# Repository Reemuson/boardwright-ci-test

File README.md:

<h1 align="center">FIC-100A</h1>

<p align="center">
  
&nbsp; &nbsp; &nbsp; &nbsp;
  
</p>

***

## SPECIFICATIONS

| Parameter | Value | 
| --- | --- |
| Revision | 0.1.3 |
| Board revision | A |
| Release version | 0.1.3 |
| Variant | RELEASED |
| Dimensions | 40.0 x 25.0 mm |

***

## OUTPUTS

Generated manufacturing, schematic, test, and release packages are published
as CI artifacts and GitHub Release assets. The repository source tree remains
the KiCad project and Boardwright workflow configuration.

***

## LEGAL

This repository contains open hardware design files, protected project branding,
and third-party workflow content.

- The primary hardware licence is listed in `LICENSE`.
- Project-specific scope notes, branding exclusions, compatibility wording,
  non-affiliation wording, and safety notes are in `NOTICE.md`.
- Third-party copyright and licence notices are preserved in
  `THIRD_PARTY_NOTICES.md`.

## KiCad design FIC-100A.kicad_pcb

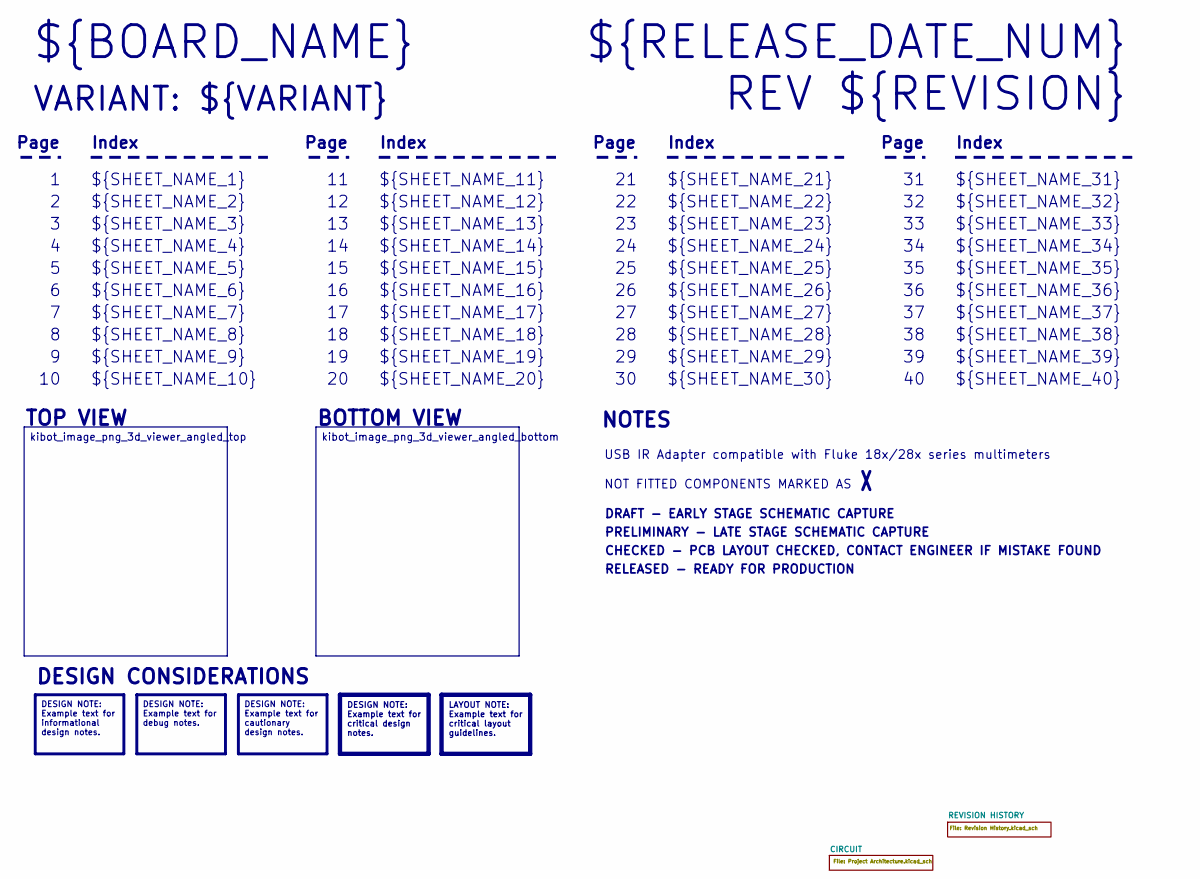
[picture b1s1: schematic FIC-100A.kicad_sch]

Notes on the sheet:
VARIANT: ${VARIANT}
RELEASED - READY FOR PRODUCTION
${SHEET_NAME_24}
Index
Page
PRELIMINARY - LATE STAGE SCHEMATIC CAPTURE
${SHEET_NAME_22}
DRAFT - EARLY STAGE SCHEMATIC CAPTURE
${SHEET_NAME_12}
${SHEET_NAME_8}
${SHEET_NAME_2}
${SHEET_NAME_5}
${SHEET_NAME_20}
${SHEET_NAME_23}
${RELEASE_DATE_NUM}
${SHEET_NAME_35}
NOT FITTED COMPONENTS MARKED AS
${SHEET_NAME_11}
${SHEET_NAME_6}
${SHEET_NAME_37}
${SHEET_NAME_26}
${SHEET_NAME_36}
REV ${REVISION}
${SHEET_NAME_15}
CHECKED - PCB LAYOUT CHECKED, CONTACT ENGINEER IF MISTAKE FOUND
BOTTOM VIEW
${SHEET_NAME_14}
${SHEET_NAME_21}
${SHEET_NAME_17}
${SHEET_NAME_18}
${SHEET_NAME_7}
${SHEET_NAME_31}
${BOARD_NAME}
NOTES
${SHEET_NAME_40}
${SHEET_NAME_39}
${SHEET_NAME_32}
${SHEET_NAME_1}
${SHEET_NAME_9}
${SHEET_NAME_38}

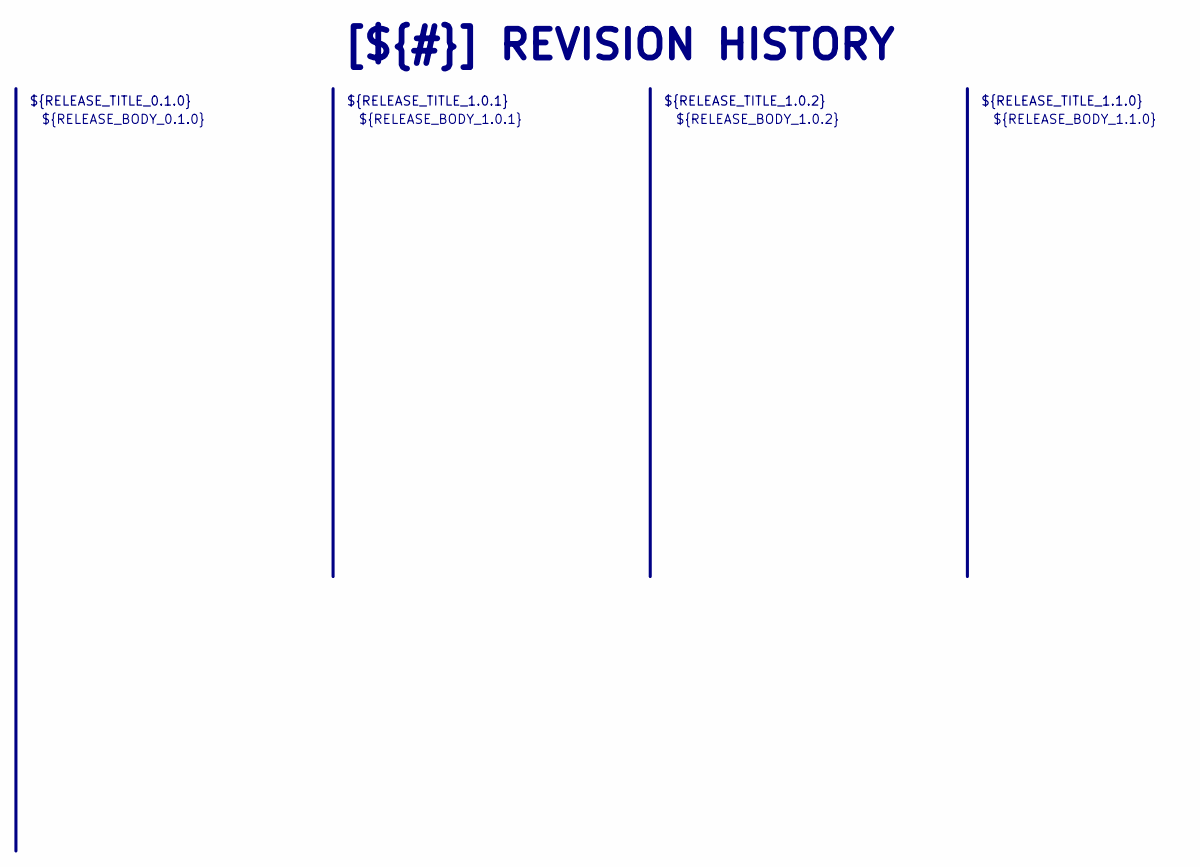
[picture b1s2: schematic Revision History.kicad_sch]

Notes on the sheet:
${RELEASE_BODY_1.1.0}
[${#}] ${TITLE}
${RELEASE_BODY_0.1.0}
${RELEASE_TITLE_1.0.2}
${RELEASE_BODY_1.0.2}
${RELEASE_BODY_1.0.1}
${RELEASE_TITLE_0.1.0}
${RELEASE_TITLE_1.0.1}
${RELEASE_TITLE_1.1.0}

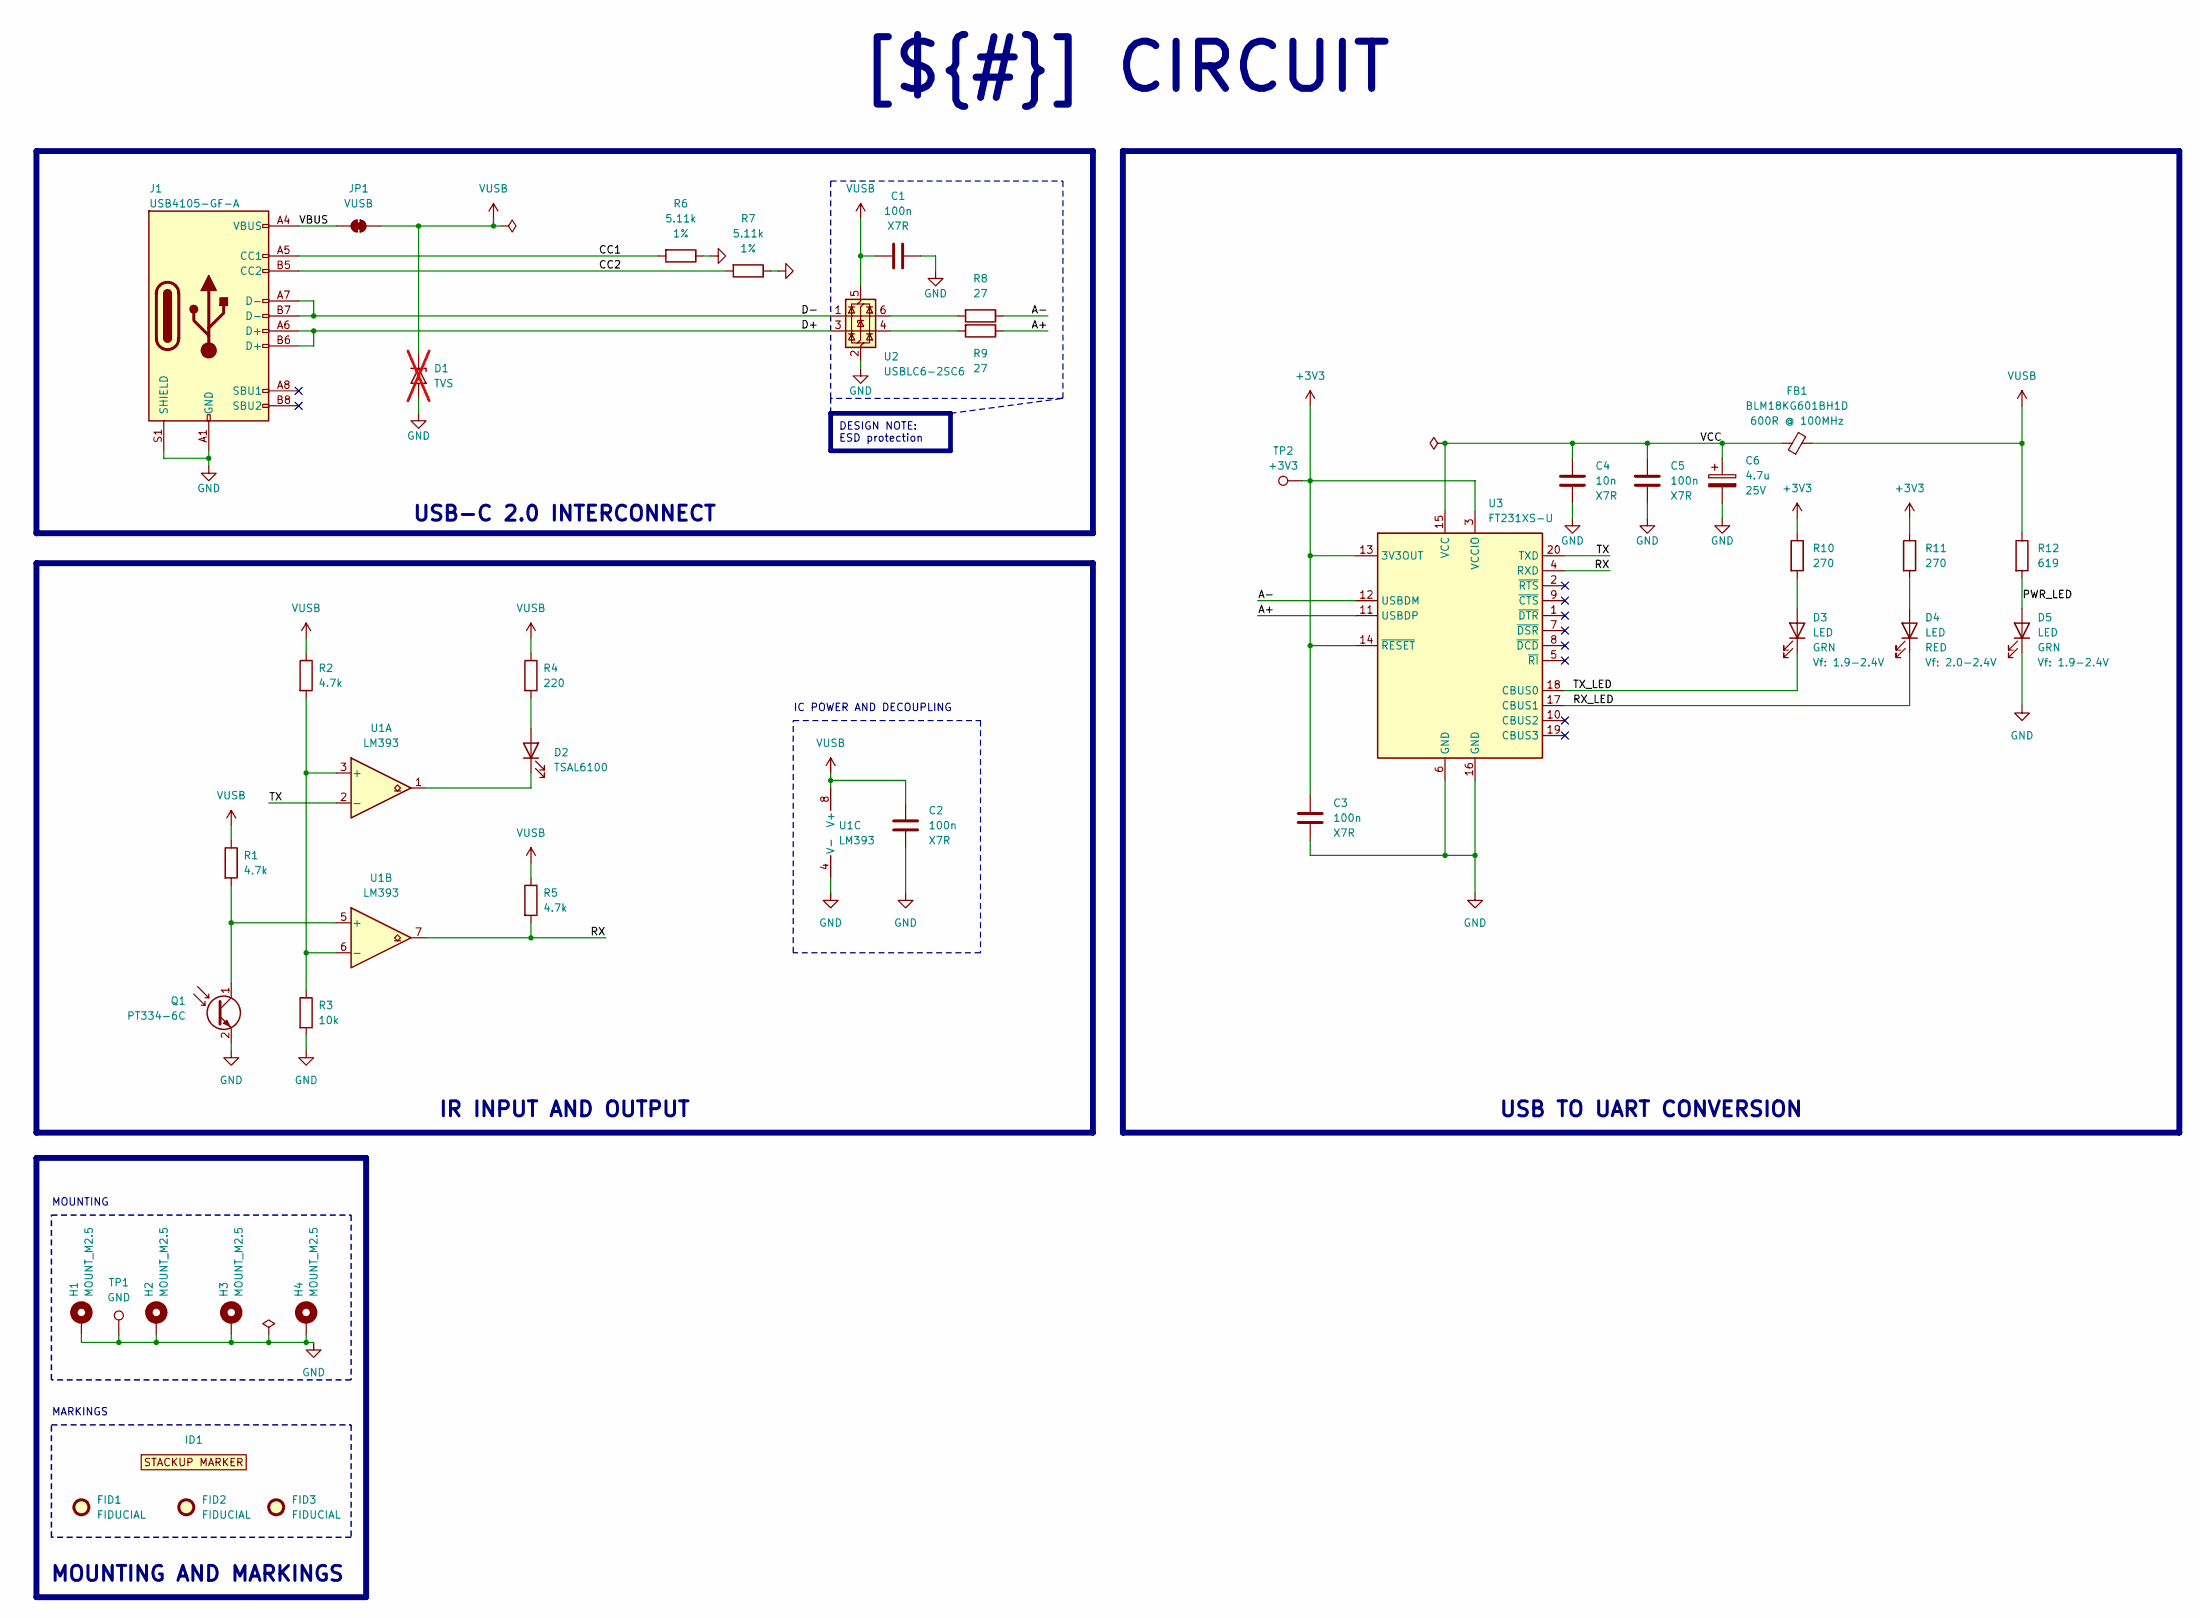
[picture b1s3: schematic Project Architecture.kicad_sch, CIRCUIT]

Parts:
C1, C2, C3, C5: 100n; C_0603_1608Metric; Voltage_Rating 16V; Tolerance 10%; MPN C1608X7R1C104KT
C4: 10n; C_0603_1608Metric; Voltage_Rating 50V; Tolerance 10%; MPN C1608X7R1H103KT
C6: 4.7u; CP_EIA-3216-18_Kemet-A; Tolerance 10%; Voltage 25V; MPN T491A475K025AT
D1: TVS; D_SMB; not fitted
D2: TSAL6100; LED_D5.0mm_IRBlack; MPN TSAL6100
D3, D5: LED; LED_0805_2012Metric; MPN LTST-C170KGKT
D4: LED; LED_0805_2012Metric; MPN LTST-C170KRKT
FB1: BLM18KG601BH1D; L_0603_1608Metric; MPN BLM18KG101JH1D
FID1, FID2, FID3: FIDUCIAL; Fiducial_1mm_Mask2mm
H1, H2, H3, H4: MOUNT_M2.5; MountingHole_2.7mm_M2.5_ISO7380_Pad
ID1: BOARD_STACKUP_MARKER; STACKUP_ID_2L_SML
J1: USB4105-GF-A; USB_C_Receptacle_GCT_USB4105-xx-A_16P_TopMnt_Horizontal; MPN USB4105-GF-A
JP1: VUSB; SolderJumper-2_P1.3mm_Bridged_Pad1.0x1.5mm
Q1: PT334-6C; LED_D5.0mm_Clear; MPN PT334-6C
R1, R2, R5: 4.7k; R_0603_1608Metric; Tolerance 1%
R3: 10k; R_0603_1608Metric; Tolerance 1%
R4: 220; R_0603_1608Metric; Tolerance 1%
R6, R7: 5.11k; R_0603_1608Metric; Tolerance 1%
R8, R9: 27; R_0603_1608Metric; Tolerance 1%
R10, R11: 270; R_0603_1608Metric; Tolerance 1%
R12: 619; R_0603_1608Metric; Tolerance 1%
TP1: GND; TestPoint_Pad_1.0x1.0mm
TP2: +3V3; TestPoint_Pad_D1.0mm
U1: LM393; SOIC-8_3.9x4.9mm_P1.27mm; MPN LM393ADT
U2: USBLC6-2SC6; SOT-23-6; MPN USBLC6-2SC6
U3: FT231XS-U; SSOP-20_3.9x8.7mm_P0.635mm; MPN FT231XS-U

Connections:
+3V3: C3.2, R10.1, R11.1, TP2.1, U3.3 (VCCIO), U3.13 (3V3OUT), U3.14 (~RESET)
/CIRCUIT/A+: R9.1, U3.11 (USBDP)
/CIRCUIT/A-: R8.1, U3.12 (USBDM)
/CIRCUIT/CC1: J1.A5 (CC1), R6.2
/CIRCUIT/CC2: J1.B5 (CC2), R7.2
/CIRCUIT/D+: J1.A6 (D+), J1.B6 (D+), U2.3 (I/O2)
/CIRCUIT/D-: J1.A7 (D-), J1.B7 (D-), U2.1 (I/O1)
/CIRCUIT/PWR_LED: D5.2 (A), R12.2
/CIRCUIT/RX: R5.2, U1.7, U3.4 (RXD)
/CIRCUIT/RX_LED: D4.1 (K), U3.17 (CBUS1)
/CIRCUIT/TX: U1.2 (-), U3.20 (TXD)
/CIRCUIT/TX_LED: D3.1 (K), U3.18 (CBUS0)
/CIRCUIT/VBUS: J1.A4 (VBUS), J1.A9 (VBUS), J1.B4 (VBUS), J1.B9 (VBUS), JP1.1 (A)
/CIRCUIT/VCC: C4.2, C5.2, C6.1, FB1.1, U3.15 (VCC)
GND: C1.1, C2.2, C3.1, C4.1, C5.1, C6.2, D1.2 (A2), D5.1 (K), H1.1, H2.1, H3.1, H4.1, J1.A1 (GND), J1.A12 (GND), J1.B1 (GND), J1.B12 (GND), J1.S1 (SHIELD), Q1.2 (E), R3.2, R6.1, R7.1, TP1.1, U1.4 (V-), U2.2 (GND), U3.6 (GND), U3.16 (GND)
unnamed: D2.2 (A), R4.2
unnamed: D2.1 (K), U1.1
unnamed: D3.2 (A), R10.2
unnamed: D4.2 (A), R11.2
unnamed: Q1.1 (C), R1.2, U1.5 (+)
unnamed: R8.2, U2.6 (I/O1)
unnamed: R9.2, U2.4 (I/O2)
unnamed: R2.2, R3.1, U1.3 (+), U1.6 (-)
VUSB: C1.2, C2.1, D1.1 (A1), FB1.2, JP1.2 (B), R1.1, R2.1, R4.1, R5.1, R12.1, U1.8 (V+), U2.5 (VBUS)

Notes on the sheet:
MOUNTING
IC POWER AND DECOUPLING
MARKINGS
DESIGN NOTE: ESD protection
IR INPUT AND OUTPUT
USB TO UART CONVERSION
USB-C 2.0 INTERCONNECT
MOUNTING AND MARKINGS
[${#}] ${TITLE}

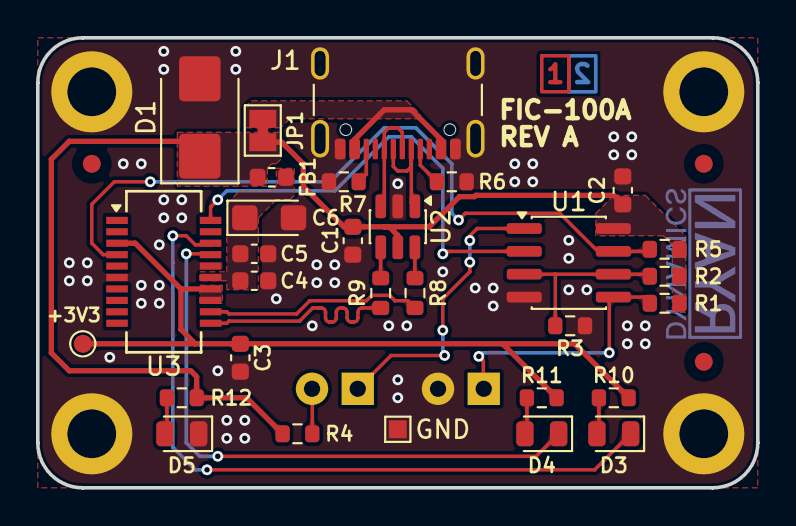
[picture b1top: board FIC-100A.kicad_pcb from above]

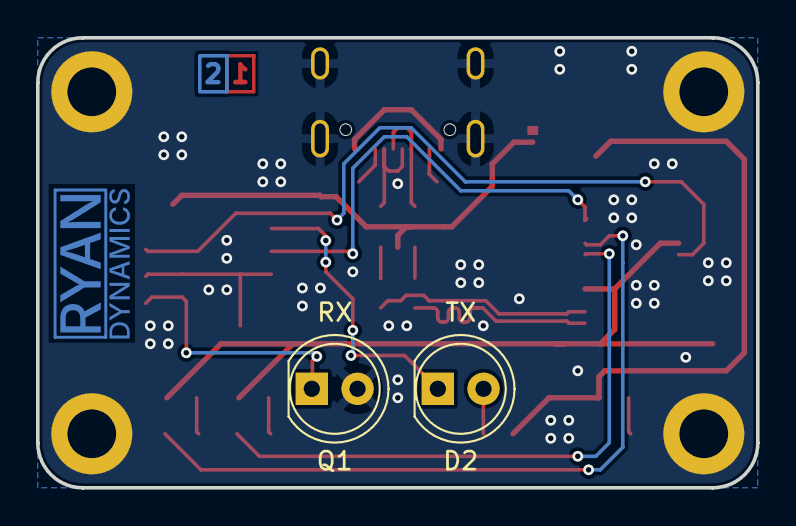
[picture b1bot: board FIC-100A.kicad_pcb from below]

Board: 2 copper layers, 40.0 x 25.0 mm, 40 parts (2 on the bottom side), 24 nets.

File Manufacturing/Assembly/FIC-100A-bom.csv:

Row,Quantity Per PCB,References,Value,Datasheet,Footprint,Description,Manufacturer,MPN,Supplier,SPN,Notes
1,1,C4,10n,https://mm.digikey.com/Volume0/opasdata/d220001/medias/docus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,C_0603_1608Metric,CAP CER 10N 50V X7R 0603,TPK,C1608X7R1H103KT,,,
2,4,C1 C2 C3 C5,100n,https://mm.digikey.com/Volume0/opasdata/d220001/medias/docus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,C_0603_1608Metric,CAP CER 100N 16V X7R 0603,TPK,C1608X7R1C104KT,,,
3,1,C6,4.7u,https://yageogroup.com/content/datasheet/asset/file/KEM_T2005_T491,CP_EIA-3216-18_Kemet-A,CAP TANT 4.7UF 10% 25V 1206,KEMET,T491A475K025AT,DigiKey,399-10128-1-ND,
4,2,D3 D5,LED,https://optoelectronics.liteon.com/upload/download/DS22-2000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,LED_0805_2012Metric,LED GRN CLEAR SMD,Lite-On Inc.,LTST-C170KGKT,DigiKey,160-1414-1-ND,Any low power green 0805 LED
5,1,D4,LED,https://optoelectronics.liteon.com/upload/download/DS-22-99-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,LED_0805_2012Metric,LED RED CLEAR SMD,Lite-On Inc.,LTST-C170KRKT,DigiKey,160-1415-1-ND,Any low power red 0805 LED
6,1,D2,TSAL6100,https://www.vishay.com/docs/81009/tsal6100.pdf,LED_D5.0mm_IRBlack,EMITTER IR 940NM 100MA RADIAL,Vishay Semiconductor Opto Division,TSAL6100,DigiKey,751-1203-ND,
7,1,FB1,BLM18KG601BH1D,https://pim.murata.com/asset/pim4/ferriteBeadInductortypefil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,L_0603_1608Metric,FERRITE BEAD 600 OHM 0603 1LN,Murata Electronics,BLM18KG101JH1D,DigiKey,490-14032-1-ND,
8,1,J1,USB4105-GF-A,https://gct.co/files/specs/usb4105-spec.pdf,USB_C_Receptacle_GCT_USB4105-xx-A_16P_TopMnt_Horizontal,CONN RCP USB2.0 TYP C 16P SMD RA,GCT,USB4105-GF-A,DigiKey,2073-USB4105-GF-ACT-ND,
9,1,Q1,PT334-6C,https://mm.digikey.com/Volume0/opasdata/d220001/medias/docus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,LED_D5.0mm_Clear,SENSOR PHOTO 940NM TOP VIEW RAD,Everlight Electronics Co Ltd,PT334-6C,DigiKey,1080-1159-ND,
10,2,R8 R9,27,https://www.analogtechnologies.com/document/New_Resistor_Kits.pdf,R_0603_1608Metric,RES 27 OHM 1% 1/10W 0603,Analog Technologies,,,,
11,1,R4,220,https://www.analogtechnologies.com/document/New_Resistor_Kits.pdf,R_0603_1608Metric,RES 220 OHM 1% 1/10W 0603,Analog Technologies,,,,
12,2,R10 R11,270,https://www.analogtechnologies.com/document/New_Resistor_Kits.pdf,R_0603_1608Metric,RES 270 OHM 1% 1/10W 0603,Analog Technologies,,,,
13,1,R12,619,https://www.analogtechnologies.com/document/New_Resistor_Kits.pdf,R_0603_1608Metric,RES 619 OHM 1% 1/10W 0603,Analog Technologies,,,,
14,3,R1 R2 R5,4.7k,https://www.analogtechnologies.com/document/New_Resistor_Kits.pdf,R_0603_1608Metric,RES 4.7K OHM 1% 1/10W 0603,Analog Technologies,,,,
15,2,R6 R7,5.11k,https://www.analogtechnologies.com/document/New_Resistor_Kits.pdf,R_0603_1608Metric,RES 5.11K OHM 1% 1/10W 0603,Analog Technologies,,,,
16,1,R3,10k,https://www.analogtechnologies.com/document/New_Resistor_Kits.pdf,R_0603_1608Metric,RES 10K OHM 1% 1/10W 0603,Analog Technologies,,,,
17,1,U3,FT231XS-U,https://ftdichip.com/wp-content/uploads/2025/06/DS_FT231X.pdf,SSOP-20_3.9x8.7mm_P0.635mm,"Full Speed USB to Full Handshake UART, SSOP-20","FTDI, Future Technology Devices International Ltd",FT231XS-U,DigiKey,768-1156-5-ND,
18,1,U1,LM393,http://www.ti.com/lit/ds/symlink/lm393.pdf,SOIC-8_3.9x4.9mm_P1.27mm,IC COMPARATOR 2 GEN PUR 8SOIC,Texas Instruments,LM393ADT,DigiKey,497-4267-1-ND,
19,1,U2,USBLC6-2SC6,https://www.st.com/resource/en/datasheet/cd00050750.pdf,SOT-23-6,TVS DIODE 5.25VWM 17VC SOT23-6,STMicroelectronics,USBLC6-2SC6,DigiKey,497-5235-1-ND,

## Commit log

2026-04-24 chore(template): prepare Boardwright CI test
2026-04-24 fix(ci): make draft preview safe for template smoke tests
2026-04-24 feat(hardware): add Boardwright CI fixture circuit
2026-04-24 fix(revision-history): improve generated entry formatting
2026-04-24 fix(schematic): read sheet titles from kicad source
2026-04-24 ci: remove legacy monolithic workflow
2026-04-24 Update Outputs
2026-04-24 release: prepare 0.1.0
2026-04-24 chore(outputs): update preview outputs
2026-04-25 release: prepare 0.1.1
2026-04-25 feat: add Boardwright-managed release orchestration
2026-04-25 release: prepare 0.1.2 (CHECKED)
2026-04-25 fix: dispatch release workflow after CI tag creation
2026-04-25 fix: keep main to README snapshot outputs
2026-04-25 release: prepare 0.1.3 (CHECKED)
2026-05-24 test: initialize boardwright live testbench
2026-05-24 test: exercise boardwright preview path
2026-05-24 fix: github workflow permission
2026-05-24 fix: hopeful pdf table fixes, non blocking tui fetch
2026-05-24 fix: kicad preflight missing files
2026-05-24 fix: kibot recursion fix?
2026-05-24 fix: refresh default project
2026-05-24 fix: more pdf fixes
2026-05-25 fix: tui test
2026-05-25 test
2026-05-25 chore(template): test 2
2026-05-25 chore(template): update project files
2026-05-25 docs(docs): update project files
2026-05-25 chore(outputs): update README snapshot
2026-05-25 release: prepare 0.1.2 (RELEASED)
2026-05-26 release: prepare 0.1.3 (RELEASED)
